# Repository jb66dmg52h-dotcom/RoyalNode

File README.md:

# RoyalNode / 2Watt Project

RoyalNode, also tracked as the 2Watt Project, is a solar-powered 915 MHz LoRa repeater carrier built around the Seeed Studio XIAO nRF52840 and EBYTE E22-900M33S high-power radio module.

> **Status:** Rev A KiCad schematic and PCB placement scaffold are active. The board is not fabrication ready.

## Locked architecture

- Standard Seeed Studio XIAO nRF52840, socketed
- EBYTE E22-900M33S radio module
- Protected 1S 3.6/3.7 V Li-ion/LiPo pack, 10-20 Ah class
- Board-mounted XT30 battery connector
- Board-mounted XT30 solar connector
- BQ25798 buck-boost charger with MPPT and power path
- Battery-mounted Semitec 103AT-2 NTC connected to BQ25798 TS network
- TPS61088 5 V boost rail for the E22
- Battery voltage and charger telemetry read directly from the BQ25798
- XIAO powered through its underside BAT and GND pads using a two-wire JST-GH lead
- LM66100 ideal diode between the main battery/system node and the XIAO BAT lead
- USB-C firmware updates through the XIAO
- USB-C battery charging through the BQ25798
- One external charge LED
- Optional MeshCore-supported BME680 environmental I2C port
- Direct controlled-impedance RF path from E22 ANT to board-edge SMA
- XIAO-controlled TPS61088 enable for radio power sequencing
- 4-layer controlled-impedance PCB

## Solar guidance

- 6 V class panel
- 20 W target for permanent deployment
- BQ25798 must be configured and validated against the selected panel's actual Vmp, Voc and Imp
- Installer must verify Vmp, Voc, Imp and cold-weather Voc

## Removed from Rev A

- MAX17048 fuel gauge and battery percentage estimation
- Power button
- eFuse
- Radio load switch
- Pogo pins
- SWD connector
- Multi-wire XIAO harness
- Extra LEDs beyond the charge LED
- Solar/USB-present telemetry
- Battery reverse-polarity circuit
- Radio-disable jumper
- Display, GPS and non-MeshCore accessory sensors
- Bench-test jumpers, simulated-temperature bypass networks and mode-selection test footprints

## Power summary

- Battery: protected 1S 3.6/3.7 V nominal, 4.20 V maximum, 10-20 Ah class
- Battery discharge capability: at least 5 A continuous, 8 A transient preferred
- Maximum charge current: 2 A
- Charge temperature sensing: battery-mounted 10 kOhm NTC; target policy suspends charging below 0 C and at/above 45 C
- Battery telemetry: BQ25798 battery voltage and charger-state measurements; no dedicated SOC fuel gauge in Rev A
- E22 rail: 5.0 V nominal
- TPS61088 rail design target: 2 A continuous
- TPS61088 inductor: Coilcraft XAL7030-222MEC, 2.2 uH
- BQ25798 inductor: Coilcraft XAL7070-222MEC, 2.2 uH
- E22 local bulk capacitance: 330-470 uF plus ceramics

## Canonical documents

- `docs/DESIGN_FREEZE_REV_A.md`
- `docs/CURRENT_STATUS_REV_A.md`
- `docs/WIRING_BLUEPRINT.md`
- `docs/ELECTRICAL_DESIGN_REV_A.md`
- `docs/LOCKED_COMPONENTS_REV_A.md`
- `docs/FINAL_POWER_CALCULATIONS_REV_A.md`
- `docs/SOLAR_DESIGN_GUIDE_REV_A.md`
- `docs/PCB_NET_CLASSES_REV_A.md`

Earlier concept documents are superseded where they conflict with the design-freeze document.

## Repository layout

```text
2Watt-Project/
├── docs/              Engineering specifications and calculations
├── hardware/          KiCad project, symbols, footprints and fabrication files
├── firmware/          Board support and hardware test firmware
├── bom/               Manufacturing and sourcing files
├── production/        Assembly and manufacturing outputs
└── test/              Bring-up procedures and measurements
```

## Local KiCad project

Open the Mac/KiCad project here:

```text
hardware/kicad/RoyalNode/RoyalNode.kicad_pro
```

Useful local checks:

```bash
make validate
make kicad-checks
```

## Remaining work

1. Resolve or formally accept the E22 footprint-library warning through the manufacturing review path.
2. Unblock the Molex edge-launch SMA footprint and final 50-ohm GCPW geometry.
3. Confirm XIAO socket orientation, XT30 polarity and connector mating clearance.
4. Refine power-stage placement from the generated ratsnest.
5. Route the PCB.
6. Run DRC, ERC, JLCPCB DFM and PCBA review.
7. Order Rev A prototypes for production validation.

## Safety and regulatory note

The radio hardware may be capable of approximately 33 dBm output. Deployed settings must comply with applicable conducted-power, antenna-gain, EIRP, bandwidth and certification requirements. The battery pack must include suitable internal protection, and deployment must respect the battery manufacturer's permitted charging-temperature range.

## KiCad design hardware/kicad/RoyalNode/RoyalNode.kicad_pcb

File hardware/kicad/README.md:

# RoyalNode KiCad Workspace

This folder contains the Git-tracked KiCad design for RoyalNode Rev A.

Open the project file:

```text
hardware/kicad/RoyalNode/RoyalNode.kicad_pro
```

Current status:

- KiCad 10.0 project scaffold created.
- Root schematic is intentionally a capture placeholder.
- PCB file contains the Rev A board outline, placement zones, RF corridor, and keepout notes.
- Project-local symbols have been started in `RoyalNode/lib_symbols/RoyalNode.kicad_sym`.
- Footprint release is controlled by `RoyalNode/lib_footprints/FOOTPRINT_RELEASE_MATRIX_REV_A.md`.
- Schematic capture should follow `RoyalNode/SCHEMATIC_CAPTURE_SEED_REV_A.csv`.
- Footprints, schematic nets, and routed copper still need to be captured from `docs/DESIGN_FREEZE_REV_A.md` and `docs/NET_MAP_REV_A.md`.

Design source of truth:

- `docs/DESIGN_FREEZE_REV_A.md`
- `docs/REFERENCE_DESIGNATORS_REV_A.md`
- `docs/NET_MAP_REV_A.md`
- `docs/PIN_AUDIT_REV_A.md`
- `docs/RF_DESIGN_REV_A.md`
- `docs/FOOTPRINT_SOURCE_LINKS_REV_A.md`
- `bom/REV_A_LOCKED_CORE_BOM.csv`
- `bom/REV_A_LOCKED_PASSIVES.csv`

Validation:

```bash
python3 tools/validate_royalnode.py
```

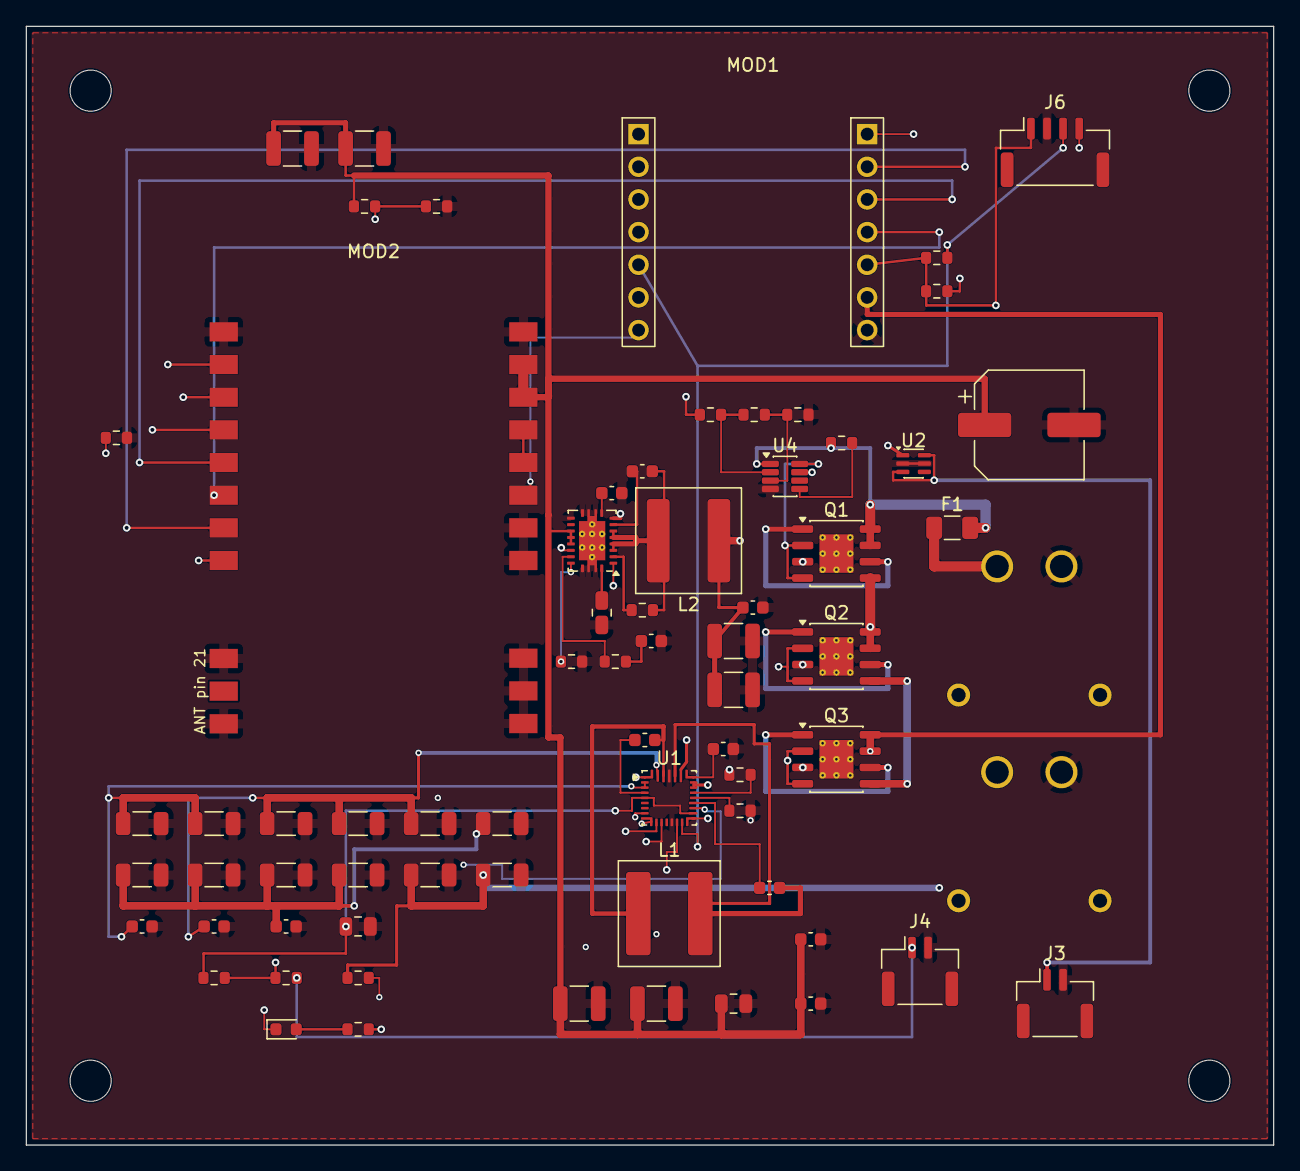
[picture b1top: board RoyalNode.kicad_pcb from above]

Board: 4 copper layers, 97.0 x 87.0 mm, 75 parts (0 on the bottom side), 55 nets.

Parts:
C200, C201, C202, C203, C204, C205, C206, C207, C208, C209, C210, C211: 10 uF 50 V; C_1206_3216Metric
C212, C213, C214, C404: 100 nF 50 V; C_0603_1608Metric
C215: 4.7 uF 25 V; C_0805_2012Metric
C216, C217: 47 nF 50 V; C_0603_1608Metric
C218: 1 nF 50 V; C_0603_1608Metric
C400, C401, C500, C501: 22 uF 16 V; C_1210_3225Metric
C402, C403: 47 uF 10 V; C_1210_3225Metric
C405: 2.2 uF; C_0805_2012Metric
C406: 100 nF; C_0603_1608Metric
C407: 47 nF; C_0603_1608Metric
C408: 4.7 nF; C_0603_1608Metric
C502: 1 uF 16 V; C_0805_2012Metric
C503: 330 uF 10 V polymer; C503_PANASONIC_10SVPC330M_8X6P9_RC
C504, C505: 100 nF 16 V; C_0603_1608Metric
D1: KT-0603R red LED; LED_0603_1608Metric
F1: Littelfuse 0483005.DR 1206 RC; F1_LITTELFUSE_483_1206_RC
J1, J2: XT30PW-M C431092 RC; J_POWER_XT30PW_M_C431092_RC
J3, J4: J_LOW_JST_GH_SM02B_GHS_TB_RC
J5: SMA edge envelope; J5_SMA_0732511150_DRAFT_ENVELOPE
J6: J_LOW_JST_GH_SM04B_GHS_TB_RC
L1: XAL7070-222MEC RC; L1_COILCRAFT_XAL7070_222MEC_RC
L2: XAL7030-222MEC RC; L2_COILCRAFT_XAL7030_222MEC_RC
MH1, MH2, MH3, MH4: M3 NPTH 3.2mm; MH_M3_NPTH_3P2MM_6P8MM_CLEARANCE
MOD1: XIAO nRF52840 socket C53202181 RC; MOD1_XIAO_NRF52840_SOCKET_C53202181_RC
MOD2: E22-900M33S C22399506 RC; MOD2_E22_900M33S_JLC_C22399506_RC
Q1, Q2, Q3: Infineon PG-DSO-8-27 thermal vias RC; Q_POWER_INFINEON_PG_DSO_8_27_RC
R100: 1.78 MOhm 1%; R_0603_1608Metric
R101: 180 kOhm 0.1%; R_0603_1608Metric
R102: 40.2 kOhm 0.1%; R_0603_1608Metric
R103, R403, R405: 100 kOhm; R_0603_1608Metric
R200: 5.23 kOhm 1%; R_0603_1608Metric
R201: 30.1 kOhm 1%; R_0603_1608Metric
R202: 100 Ohm; R_0603_1608Metric
R203: 4.70 kOhm 1%; R_0603_1608Metric
R204, R205, R206: 10 kOhm; R_0603_1608Metric
R207: 2.2 kOhm 1%; R_0603_1608Metric
R400: 176 kOhm 0.1%; R_0603_1608Metric
R401: 56.0 kOhm 0.1%; R_0603_1608Metric
R402: 330 kOhm; R_0603_1608Metric
R404: 20.0 kOhm; R_0603_1608Metric
U1: BQ25798 RQM0029A RC; U1_BQ25798_RQM0029A_RC
U2: LM66100 DCK0006A SC70-6 RC; U2_LM66100_DCK0006A_SC70_6_RC
U3: TPS61088 RHL0020A thermal vias RC; U3_TPS61088_RHL0020A_THERMALVIAS_RC
U4: LTC4365 TSOT-23-8 RC; U4_LTC4365_TSOT23_8_RC

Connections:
3V3: D1.1 (Terminal 1), J6.1 (3V3), MOD1.3V3, R204.1 (Terminal 1), R205.1 (Terminal 1), R206.1 (Terminal 1)
5V_RADIO: C402.1 (Terminal 1), C403.1 (Terminal 1), C500.1 (Terminal 1), C501.1 (Terminal 1), C502.1 (Terminal 1), C503.1 (Terminal 1), C504.1 (Terminal 1), C505.1 (Terminal 1), MOD2.9 (VCC), MOD2.10 (VCC), R400.1 (Terminal 1), U3.14 (VOUT), U3.15 (VOUT), U3.16 (VOUT)
BATP_KELVIN: R202.2 (Terminal 2), U1.18 (BATP)
BAT_RAW: C210.1 (Terminal 1), C211.1 (Terminal 1), J2.1 (PLUS), R202.1 (Terminal 1), U1.22 (BAT), U1.23 (BAT), U2.1 (VIN)
BOOST_BOOT: C406.1 (Terminal 1), U3.8 (BOOT)
BOOST_COMP: R404.1 (Terminal 1), U3.18 (COMP)
BOOST_COMP_RC: C408.1 (Terminal 1), R404.2 (Terminal 2)
BOOST_EN: MOD1.D7 (D7/P1.12), R405.1 (Terminal 1), U3.2 (EN)
BOOST_FB: R400.2 (Terminal 2), R401.1 (Terminal 1), U3.17 (FB)
BOOST_FSW: R402.1 (Terminal 1), U3.3 (FSW)
BOOST_ILIM: R403.1 (Terminal 1), U3.19 (ILIM)
BOOST_SS: C407.1 (Terminal 1), U3.10 (SS)
BOOST_SW: C406.2 (Terminal 2), L2.2 (Terminal 2), R402.2 (Terminal 2), U3.4 (SW), U3.5 (SW), U3.6 (SW), U3.7 (SW)
BOOST_VCC: C405.1 (Terminal 1), U3.1 (VCC)
BQ_ACDRV1: Q2.2 (G1), Q2.4 (G2), U1.11 (ACDRV1)
BQ_ACDRV2: Q3.2 (G1), Q3.4 (G2), U1.10 (ACDRV2)
BQ_BTST1: C216.1 (Terminal 1), U1.4 (BTST1)
BQ_BTST2: C217.1 (Terminal 1), U1.19 (BTST2)
BQ_INT: R204.2 (Terminal 2), U1.21 (INT)
BQ_PMID: C202.1 (Terminal 1), C203.1 (Terminal 1), C204.1 (Terminal 1), C213.1 (Terminal 1), U1.29 (PMID)
BQ_PROG: R203.1 (Terminal 1), U1.20 (PROG)
BQ_REGN: C215.1 (Terminal 1), R200.1 (Terminal 1), U1.5 (REGN), U1.17 (ILIM_HIZ)
BQ_SDRV: C218.1 (Terminal 1), U1.24 (SDRV)
BQ_SOLAR_SELECTOR_COMMON: Q2.1 (S1), Q2.6 (S2)
BQ_STAT: R207.2 (Terminal 2), U1.1 (STAT)
BQ_SW1: C216.2 (Terminal 2), L1.1 (Terminal 1), U1.28 (SW1)
BQ_SW2: C217.2 (Terminal 2), L1.2 (Terminal 2), U1.26 (SW2)
BQ_SYS: C205.1 (Terminal 1), C206.1 (Terminal 1), C207.1 (Terminal 1), C208.1 (Terminal 1), C209.1 (Terminal 1), C214.1 (Terminal 1), C400.1 (Terminal 1), C401.1 (Terminal 1), C404.1 (Terminal 1), L2.1 (Terminal 1), U1.25 (SYS), U3.9 (VIN)
BQ_TS: R200.2 (Terminal 2), R201.1 (Terminal 1), U1.16 (TS)
BQ_USB_SELECTOR_COMMON: Q3.1 (S1), Q3.6 (S2)
BQ_VBUS: C200.1 (Terminal 1), C201.1 (Terminal 1), C212.1 (Terminal 1), Q2.3 (D2), Q2.5 (D2), Q3.3 (D2), Q3.5 (D2), U1.2 (VBUS), U1.3 (VBUS)
CHG_LED_K: D1.2 (Terminal 2), R207.1 (Terminal 1)
E22_BUSY: MOD1.D2 (D2/P0.28), MOD2.14 (BUSY)
E22_DIO1: MOD1.D1 (D1/P0.03), MOD2.13 (DIO1)
E22_NRST: MOD1.D0 (D0/P0.02), MOD2.15 (NRST)
E22_NSS: MOD1.D3 (D3/P0.29), MOD2.19 (NSS)
E22_RXEN: MOD1.D6 (D6/P1.11), MOD2.6 (RXEN)
E22_TXEN_DIO2: MOD2.7 (TXEN), MOD2.8 (DIO2)
GND: C200.2 (Terminal 2), C201.2 (Terminal 2), C202.2 (Terminal 2), C203.2 (Terminal 2), C204.2 (Terminal 2), C205.2 (Terminal 2), C206.2 (Terminal 2), C207.2 (Terminal 2), C208.2 (Terminal 2), C209.2 (Terminal 2), C210.2 (Terminal 2), C211.2 (Terminal 2), C212.2 (Terminal 2), C213.2 (Terminal 2), C214.2 (Terminal 2), C215.2 (Terminal 2), C218.2 (Terminal 2), C400.2 (Terminal 2), C401.2 (Terminal 2), C402.2 (Terminal 2), C403.2 (Terminal 2), C404.2 (Terminal 2), C405.2 (Terminal 2), C407.2 (Terminal 2), C408.2 (Terminal 2), C500.2 (Terminal 2), C501.2 (Terminal 2), C502.2 (Terminal 2), C503.2 (Terminal 2), C504.2 (Terminal 2), C505.2 (Terminal 2), J1.2 (MINUS), J2.2 (MINUS), J3.2 (PIN2), J4.2 (PIN2), J6.2 (GND), MOD1.GND, MOD2.1 (GND), MOD2.2 (GND), MOD2.3 (GND), MOD2.4 (GND), MOD2.5 (GND), MOD2.11 (GND), MOD2.12 (GND), MOD2.20 (GND), MOD2.22 (GND), R102.2 (Terminal 2), R203.2 (Terminal 2), R401.2 (Terminal 2), R403.2 (Terminal 2), R405.2 (Terminal 2), U1.13 (CE), U1.27 (GND), U2.2 (GND), U2.5 (ST), U3.11 (NC_GND), U3.12 (NC_GND), U3.20 (AGND), U3.21 (PGND_EP), U4.4 (GND)
I2C_SCL: J6.4 (SCL), MOD1.D5 (D5/P0.05), R206.2 (Terminal 2), U1.14 (SCL)
I2C_SDA: J6.3 (SDA), MOD1.D4 (D4/P0.04), R205.2 (Terminal 2), U1.15 (SDA)
LTC_SHDN: R103.2 (Terminal 2), U4.5 (SHDN)
NTC_SENSE: J4.1 (PIN1), R201.2 (Terminal 2)
OV_NODE: R101.2 (Terminal 2), R102.1 (Terminal 1), U4.3 (OV)
SOLAR_FUSED: F1.2 (Terminal 2), Q1.7 (D1), Q1.8 (D1), R100.1 (Terminal 1), R103.1 (Terminal 1), U4.1 (VIN)
SOLAR_PROTECTED: Q1.3 (D2), Q1.5 (D2), Q2.7 (D1), Q2.8 (D1), U1.9 (VAC1), U4.7 (VOUT)
SOLAR_PROT_COMMON: Q1.1 (S1), Q1.6 (S2)
SOLAR_PROT_GATE: Q1.2 (G1), Q1.4 (G2), U4.8 (GATE)
SOLAR_RAW: F1.1 (Terminal 1), J1.1 (PLUS)
SPI_MISO: MOD1.D9 (D9/P1.14), MOD2.16 (MISO)
SPI_MOSI: MOD1.D10 (D10/P1.15), MOD2.17 (MOSI)
SPI_SCK: MOD1.D8 (D8/P1.13), MOD2.18 (SCK)
USB_VBUS_RAW: MOD1.5V (5V/VBUS), Q3.7 (D1), Q3.8 (D1), U1.8 (VAC2)
UV_NODE: R100.2 (Terminal 2), R101.1 (Terminal 1), U4.2 (UV)
XIAO_BAT_ISO: J3.1 (PIN1), U2.3 (CE), U2.6 (VOUT)

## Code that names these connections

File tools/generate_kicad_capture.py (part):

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PWR_FLAG_SYMBOL = "RoyalNode:RN_PWR_FLAG"
PWR_FLAGS = [
    ("PF1", "GND", (15.24, 241.30)),
    ("PF2", "USB_VBUS_RAW", (15.24, 248.92)),
    ("PF3", "SOLAR_FUSED", (15.24, 256.54)),
    ("PF4", "SOLAR_PROTECTED", (15.24, 264.16)),
    ("PF5", "BAT_RAW", (15.24, 271.78)),
    ("PF6", "BQ_VBUS", (15.24, 279.40)),
]


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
